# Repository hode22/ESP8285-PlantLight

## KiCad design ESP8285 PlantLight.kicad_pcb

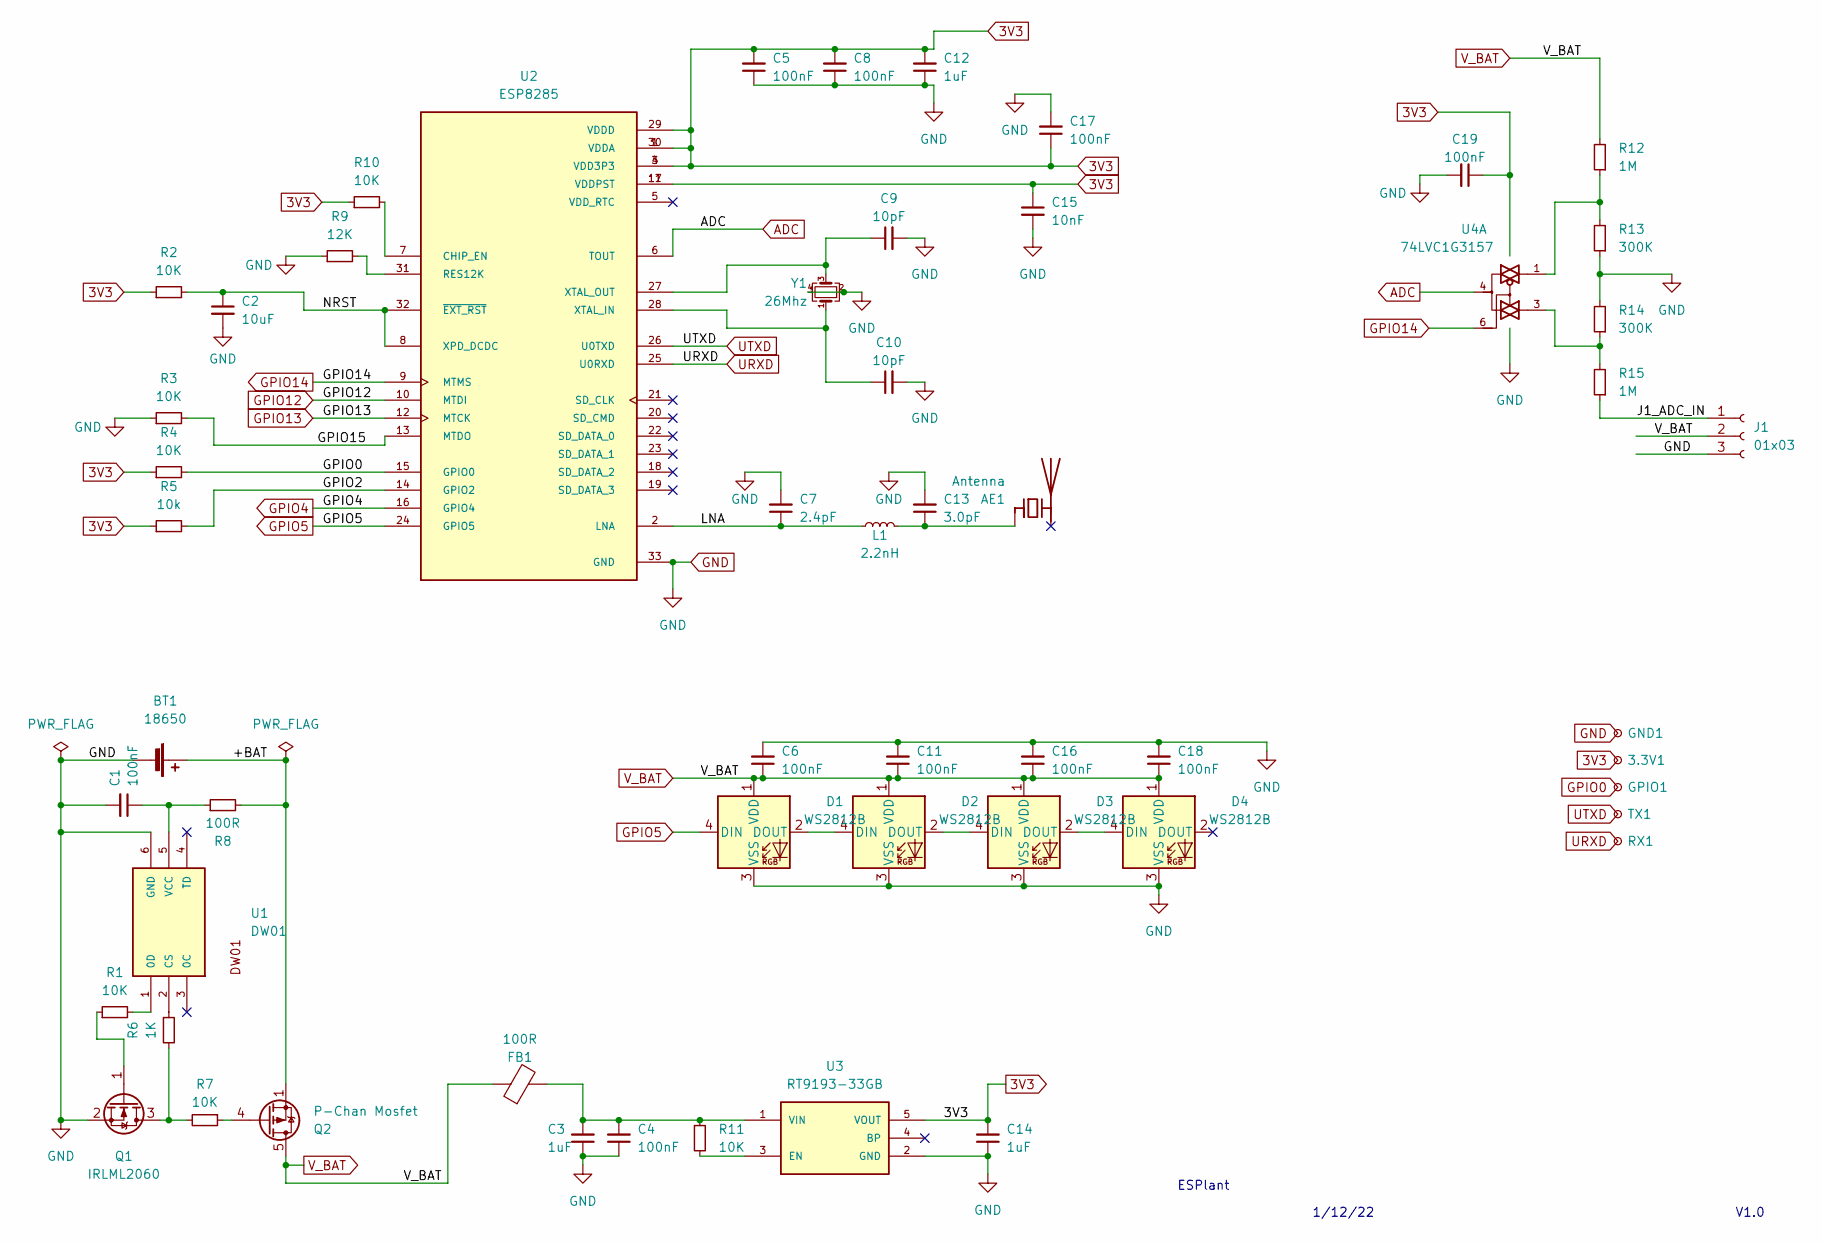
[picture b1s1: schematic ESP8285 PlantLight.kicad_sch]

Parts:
3.3V1: TestPoint_Small; TestPoint_Pad_D1.0mm
AE1: Antenna; Johanson_2450AT43F0100
BT1: 18650; 18650_footprint
C1, C4, C5, C6, C8, C11, C16, C17, C18, C19: 100nF; C_0402_1005Metric
C2: 10uF; C_0603_1608Metric
C3, C12, C14: 1uF; C_0603_1608Metric
C7: 2.4pF; C_01005_0402Metric
C9, C10: 10pF; C_01005_0402Metric
C13: 3.0pF; C_01005_0402Metric
C15: 10nF; C_0402_1005Metric
D1, D2, D3, D4: WS2812B; LED_WS2812B_PLCC4_5.0x5.0mm_P3.2mm
FB1: 100R; R_0603_1608Metric
GND1: TestPoint_Small; TestPoint_Pad_D1.0mm
GPIO1: TestPoint_Small; TestPoint_Pad_D1.0mm
J1: 01x03; PinHeader_1x03_P2.54mm_Vertical
L1: 2.2nH; L_01005_0402Metric
Q1: IRLML2060; SOT-23
Q2: P-Chan Mosfet; VSON-8_3.3x3.3mm_P0.65mm_NexFET
R1: 10K; C_0402_1005Metric
R2: 10K; R_01005_0402Metric
R3, R4, R7, R10, R11: 10K; R_0402_1005Metric
R5: 10k; R_0402_1005Metric
R6: 1K; R_0402_1005Metric
R8: 100R; R_0402_1005Metric
R9: 12K; R_0402_1005Metric
R12, R15: 1M; C_0402_1005Metric
R13, R14: 300K; R_0402_1005Metric
RX1: TestPoint_Small; TestPoint_Pad_D1.0mm
TX1: TestPoint_Small; TestPoint_Pad_D1.0mm
U1: DW01; SOT23-6
U2: ESP8285; QFN50P500X500X90-33N; PARTREV 2.0
U3: RT9193-33GB; SOT94P279X129-5N
U4: 74LVC1G3157; SOP95P275X110-6N
Y1: 26Mhz; Crystal_SMD_3225-4Pin_3.2x2.5mm

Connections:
3V3: 3.3V1.1, C5.2, C8.2, C12.2, C14.2, C15.1, C17.1, C19.1, R2.1, R4.1, R5.1, R10.1, U2.1 (VDDA), U2.3 (VDD3P3), U2.4 (VDD3P3), U2.11 (VDDPST), U2.17 (VDDPST), U2.29 (VDDD), U2.30 (VDDA), U3.5 (VOUT), U4.5 (VCC)
/+BAT: BT1.1 (+), Q2.1 (S), Q2.2 (S), Q2.3 (S), R8.2
/GPIO2: R5.2, U2.14 (GPIO2)
/GPIO15: R3.2, U2.13 (MTDO)
/J1_ADC_IN: J1.1, R15.1
/LNA: C7.1, L1.1, U2.2 (LNA)
/NRST: C2.1, R2.2, U2.8 (XPD_DCDC), U2.32 (~EXT_RST)
ADC: U2.6 (TOUT), U4.4
GND: BT1.2 (-), C1.2, C2.2, C3.1, C4.1, C5.1, C6.2, C7.2, C8.1, C9.2, C10.2, C11.2, C12.1, C13.2, C14.1, C15.2, C16.2, C17.2, C18.2, C19.2, D1.3 (VSS), D2.3 (VSS), D3.3 (VSS), D4.3 (VSS), GND1.1, J1.3, Q1.2 (S), R3.1, R9.1, R13.1, R14.2, U1.6 (GND), U2.33 (GND), U3.2 (GND), U4.2 (GND), Y1.2, Y1.4
GPIO0: GPIO1.1, R4.2, U2.15 (GPIO0)
GPIO4: U2.16 (GPIO4)
GPIO5: D1.4 (DIN), U2.24 (GPIO5)
GPIO12: U2.10 (MTDI)
GPIO13: U2.12 (MTCK)
GPIO14: U2.9 (MTMS), U4.6
unnamed: AE1.1 (FEED), C13.1, L1.2
unnamed: C1.1, R8.1, U1.5 (VCC)
unnamed: C3.2, C4.2, FB1.2, R11.1, U3.1 (VIN)
unnamed: C9.1, U2.27 (XTAL_OUT), Y1.3
unnamed: C10.1, U2.28 (XTAL_IN), Y1.1
unnamed: D1.2 (DOUT), D2.4 (DIN)
unnamed: D2.2 (DOUT), D3.4 (DIN)
unnamed: D3.2 (DOUT), D4.4 (DIN)
unnamed: Q1.1 (G), R1.1
unnamed: Q1.3 (D), R6.2, R7.2
unnamed: Q2.4 (G), R7.1
unnamed: R1.2, U1.1 (0D)
unnamed: R6.1, U1.2 (CS)
unnamed: R9.2, U2.31 (RES12K)
unnamed: R10.2, U2.7 (CHIP_EN)
unnamed: R11.2, U3.3 (EN)
unnamed 31: R12.1, R13.2, U4.1; also elsewhere on the board
unnamed: R14.1, R15.2, U4.3
URXD: RX1.1, U2.25 (U0RXD)
UTXD: TX1.1, U2.26 (U0TXD)
V_BAT: C6.1, C11.1, C16.1, C18.1, D1.1 (VDD), D2.1 (VDD), D3.1 (VDD), D4.1 (VDD), FB1.1, J1.2, Q2.5 (D), R12.2; also elsewhere on the board

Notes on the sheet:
ESPlant
V1.0
1/12/22

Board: 2 copper layers, 56 parts (0 on the bottom side), 33 nets, no tracks yet.

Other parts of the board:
R12#2: 1M; C_0402_1005Metric

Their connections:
unnamed 31: R12#2.1; also elsewhere on the board
V_BAT: R12#2.2; also elsewhere on the board

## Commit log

2022-12-03 space session
2022-12-03 sat session
2022-12-06 mon session
2022-12-11 sun session
2022-12-13 tue session
2022-12-14 wed session
